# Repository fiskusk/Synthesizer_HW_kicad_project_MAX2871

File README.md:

# Synthesizer_HW_kicad_project_MAX2871
Synthesizer KiCad project for **MAX2871**. Controled by **STM32F042F6G6**.

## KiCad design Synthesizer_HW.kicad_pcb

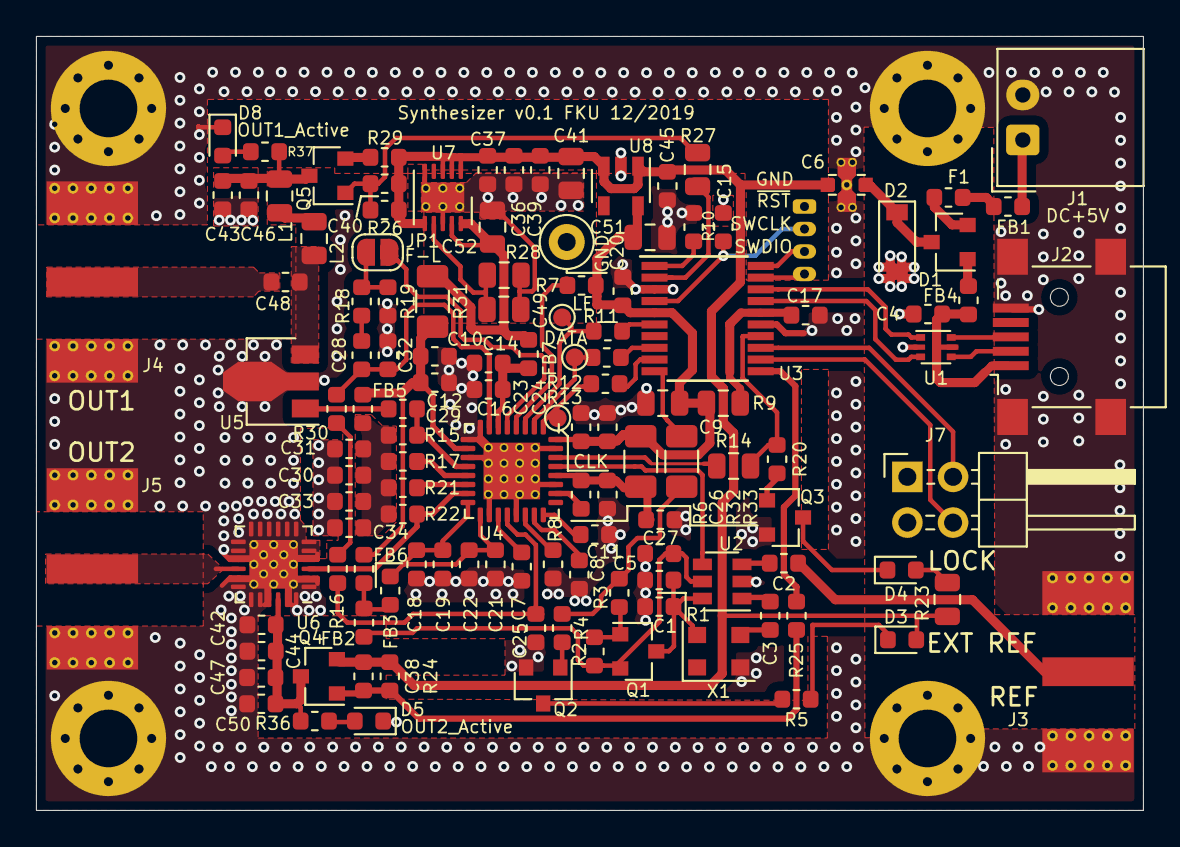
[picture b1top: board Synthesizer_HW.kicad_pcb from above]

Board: 2 copper layers, 61.5 x 43.0 mm, 131 parts (1 on the bottom side), 82 nets.

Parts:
C1, C5, C10, C14, C15, C17, C18, C20, C22, C24, C27, C30, C33, C38, C39, C40: 100n; C_0603_1608Metric
C2, C3, C36, C46, C47: 1n; C_0603_1608Metric
C4, C7, C8, C11, C45, C50: 1u; C_0603_1608Metric
C6: NFM18PS105; NFM18PS_Series
C9, C51: 4u7; C_0805_2012Metric
C12, C16, C19, C21, C23, C26, C31, C34, C43, C44: 10p; C_0603_1608Metric
C25: 1n2; C_0603_1608Metric
C28: 47n; C_0603_1608Metric
C29, C37, C48: 100p; C_0603_1608Metric
C32: 2n7; C_0603_1608Metric
C41, C52: 10u; C_0805_2012Metric
C42: 2p2; C_0603_1608Metric
C49: 470n; C_0805_2012Metric
D1: BAT54C; SOT-23
D2: PTVS3V3S1UR.115; D_SOD-123
D3, D4, D5, D8: LG L29K-F2J1-24; LED_0603_1608Metric
F1: ERBRE0R50V; Fuse_0603_1608Metric
FB1, FB2, FB3, FB4, FB5, FB6, FB7: BLM18PG471; L_0603_1608Metric
H1, H2, H3, H4: MountingHole_Pad; MountingHole_3.2mm_M3_Pad_Via
J1: +5V_DC; Molex_SPOX_5268-02A_1x02_P2.50mm_Horizontal
J2: USB_B_Mini; USB_Mini-B_Lumberg_2486_01_Horizontal
J3: EXT_REF_IN; SMA_Molex_73251-1153_EdgeMount_Horizontal
J4: RF OUT1; SMA_Molex_73251-1153_EdgeMount_Horizontal
J5: RF OUT2; SMA_Molex_73251-1153_EdgeMount_Horizontal
J6: SWD; Molex_PicoBlade_53047-0410_1x04_P1.25mm_Vertical
J7: Selector; PinHeader_2x02_P2.54mm_Horizontal
JP1: Fast-Lock; SolderJumper-2_P1.3mm_Open_RoundedPad1.0x1.5mm
L1: 68n; L_0805_2012Metric
L2: 3n3; L_0805_2012Metric
Q1: BC857; SOT-23
Q2, Q3: BC847; SOT-23
Q4, Q5: IRLML5203; SOT-23
R1, R2, R8: 4k7; R_0603_1608Metric
R3, R4, R6, R7, R10, R20: 10k; R_0603_1608Metric
R5, R11, R12, R13, R36, R37: 1k; R_0603_1608Metric
R9: 0R; R_0805_2012Metric
R14, R23: 1k; R_0805_2012Metric
R15, R17, R21, R22: 49R9; R_0603_1608Metric
R16: 680R; R_0603_1608Metric
R18: 360R; R_0603_1608Metric
R19, R30: 0R; R_0603_1608Metric
R24, R26: 910k; R_0603_1608Metric
R25: 47k; R_0603_1608Metric
R27: 47k; R_0805_2012Metric
R28: 33.2k; R_0805_2012Metric
R29: 4R7; R_0603_1608Metric
R31, R32, R33: 0R; R_1206_3216Metric
TP1: PLO_LE; TestPoint_Pad_D1.0mm
TP2: PLO_DATA; TestPoint_Pad_D1.0mm
TP3: PLO_CLK; TestPoint_Pad_D1.0mm
TP7: GND; TestPoint_Loop_D1.80mm_Drill1.0mm_Beaded
U1: USBLC6-2; SOT-666
U2: SN74LVC1G3157; SOT-23-6
U3: STM32F042F6Px; TSSOP-20_4.4x6.5mm_P0.65mm
U4: MAX2871; TQFN-32-1EP_5x5mm_P0.5mm_EP3.15x3.15mm_ThermalVias
U5: GVA-63+; SOT-89-3
U6: XX1002-QH; QFN-24-1EP_4x4mm_P0.5mm_EP2.7x2.7mm_ThermalVias
U7: LT3042xMSE; DFN-10-1EP_3x3mm_P0.5mm_EP1.65x2.38mm_ThermalVias
U8: LP5907MFX-3.3; SOT-23-5
X1: TXETALSANF-10MHz; Crystal_SMD_4Pin_3.2x2.5mm

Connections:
+5V: C6.3, C36.1, C37.1, C38.1, C39.1, C40.1, C41.1, C45.1, D3.2, Q4.2, R23.1, R24.2, R26.2, R29.2, U7.1, U7.2, U7.3, U7.6, U8.1, U8.3
/DOUBLER_EN: R25.1, U3.11
/INT_REF: R3.2, R4.2, R32.1
/PLO_CLK: R13.1, TP3.1, U4.1
/PLO_DATA: R12.1, TP2.1, U4.2
/PLO_LE: R11.1, TP1.1, U4.3
/PLO_MUXOUT: R14.1, R20.2, U3.14
/RFOUTA: C29.1, U5.1
/RFOUTB: R22.2, U4.15, U6.3
/RF_OUT_EN: R27.2, U3.2
/SWCLK: J6.3, U3.20
/SWDIO: J6.4, U3.19
/USB_D+: U1.1, U3.18
/USB_D-: U1.3, U3.17
/VDD1: C26.1, C27.2, R6.2, R33.2, U4.28
/~RST: C15.2, J6.2, U3.4
GND: C1.2, C4.2, C5.2, C6.2, C7.2, C8.2, C9.1, C10.1, C11.2, C12.2, C14.1, C15.1, C16.2, C17.2, C18.1, C19.2, C20.1, C21.2, C22.1, C23.2, C24.1, C25.2, C26.2, C27.1, C30.1, C31.2, C32.2, C33.1, C34.2, C36.2, C37.2, C39.2, C41.2, C42.1, C43.1, C44.1, C45.2, C46.1, C47.1, C49.1, C50.2, C51.2, C52.2, D2.2, D5.1, D8.1, H1.1, H2.1, H3.1, H4.1, J1.2, J2.5, J2.6, J3.2, J4.2, J5.2, J6.1, J7.1, J7.3, Q2.2, Q3.2, R1.2, R8.1, R10.1, R19.1, R28.1, TP7.1, U1.2, U2.2, U3.3, U3.15, U4.8, U4.9, U4.11, U4.18, U4.21, U4.27, U4.31, U4.33, U5.2, U6.1, U6.2, U6.4, U6.5, U6.6, U6.7, U6.8, U6.9, U6.10, U6.11, U6.12, U6.13, U6.14, U6.15, U6.17, U6.18, U6.19, U6.20, U6.21, U6.23, U6.24, U6.25, U7.5, U7.8, U7.11, U8.2, X1.2
unnamed: C1.1, Q1.3, R1.1, U2.6, X1.4
unnamed: C2.1, U2.3
unnamed: C2.2, J3.1
unnamed: C3.1, X1.3
unnamed: C3.2, U2.1
unnamed: C5.1, FB2.2, Q1.2, R2.2, U2.5
unnamed: C6.1, D1.3, D2.1
unnamed: C7.1, U4.19
unnamed: C8.1, U4.23
unnamed: C10.2, C12.1, FB5.1, FB6.2, R31.2, U4.10
unnamed: C11.1, U4.24
unnamed: C14.2, C16.1, FB7.2, U4.6
unnamed: C17.1, R9.1, U3.16
unnamed: C18.2, C19.1, C21.1, C22.2, FB3.2, U4.16, U4.17
unnamed: C25.1, R16.1, U4.20
unnamed: C28.1, C32.1, R30.2, U4.7
unnamed: C28.2, R18.1
unnamed: C29.2, R15.2, U4.12
unnamed: C30.2, C31.1, C33.2, C34.1, FB5.2, R15.1, R17.1, R21.1, R22.1
unnamed: C38.2, Q4.1, R24.1, R25.2
unnamed: C40.2, Q5.1, R26.1, R27.1
unnamed: C42.2, C44.2, C47.2, C50.1, Q4.3, R36.2, U6.22
unnamed: C43.2, C46.2, L1.1, Q5.3, R37.2
unnamed: C48.1, J4.1
unnamed: C48.2, L2.2, U5.3
unnamed: C49.2, R28.2, U7.7
unnamed: D1.1, FB4.2
unnamed: D1.2, F1.1
unnamed: D3.1, R5.2
unnamed: D4.1, Q3.3
unnamed: D4.2, R23.2
unnamed: D5.2, R36.1
unnamed: D8.2, R37.1
unnamed: F1.2, FB1.1
unnamed: FB1.2, J1.1
unnamed: FB2.1, FB3.1, FB6.1
unnamed: J2.2, U1.4
unnamed: J2.3, U1.6
unnamed: J5.1, U6.16
unnamed: J7.2, U3.13
unnamed: J7.4, U3.12
unnamed: JP1.1, U4.5
unnamed: JP1.2, R18.2, R19.2
unnamed: L1.2, L2.1
unnamed: Q1.1, R2.1, R3.1
unnamed: Q2.1, R4.1
unnamed: Q2.3, R5.1
unnamed: Q3.1, R20.1
unnamed: Q5.2, R29.1
unnamed: R6.1, U4.26
unnamed: R7.1, U4.4
unnamed: R8.2, U4.22
unnamed: R10.2, U3.1
unnamed: R11.2, U3.6
unnamed: R12.2, U3.8
unnamed: R13.2, U3.9
unnamed: R14.2, U4.30
unnamed: R16.2, R30.1
unnamed: R17.2, U4.13
unnamed: R21.2, U4.14
unnamed: R32.2, U3.10
unnamed: U2.4, U4.29
VBUS: C4.1, FB4.1, J2.1, U1.5
VDD: C9.2, C20.2, C23.1, C24.2, C51.1, R7.2, R9.2, R33.1, U3.5, U4.32, U8.5
VDDA: C52.1, FB7.1, R31.1, U7.9, U7.10

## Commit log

2019-11-17 Edited gitignore for desktop.ini, created README
2019-11-17 Initial load kicad project files
2019-11-22 deleted *.sch-bak and updated gitignore
2019-11-22 schema drawed and board wip
2019-11-24 board WIP, now editing silkscreen
2019-11-26 first almost done version, with debug interface,
2019-11-27 Updated gitignore for documentation, gerber folde
2019-11-27 latest vers., after correc., added moun. holes
2019-11-29 last version-send to prof. with dimensions
2019-12-04 version v0.1 for fabrication
2019-12-06 some changes in schematic
